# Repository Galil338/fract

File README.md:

# Fract Keyboard

Fract is a 34 key ortholinear keyboard, powered by a bluetooth-enabled Pro Micro compatible dev board.

It uses Choc v1 keyswitches with 18mm x 17mm spacing.

The goal of this design was to build a simple pocketable keyboard out of PCBs.

## Project structure

* [`gerbers`](gerbers): Gerber files for PCB manufacturing
* [`graphics`](graphics): Source assets for PCB silkscreen
* [`kicad`](kicad): KiCad project files (schematics and PCB designs)
* [`kicad-libraries`](kicad-libraries): KiCad components and footprints
* [`images`](images): Images for project documentation

## PCBs

**Each build uses two copies of the main PCB and two copies of the top plate PCB.**

The main PCB is used as the logical PCB. A second copy of the main PCB is used a bottom plate, by flipping it the long way and screwing it directly to the logical PCB.

Two copies of the top plate PCB cover the dev board and battery. Flip this PCB as well. It has a cutout which fits the reset button on the left, and the power switch on the right.

## Keyboard firmware

* ZMK
    * Fract shield definition is in [skarrmann's zmk-config](https://github.com/skarrmann/zmk-config)

## Bill of materials

Part | Purpose | Quantity | Notes
---- | ------- | -------- | ---------
Main PCB  | logical PCB, bottom plate | 2 | Send Gerber zip files to [JLCPCB](https://jlcpcb.com/)
Top plate PCB  | cover dev board and battery  | 2 | 
Bluetooth Pro Micro | Microcontroller board | 1 | nice!nano or SuperMini nRF52840
502040 LiPo Battery | Powers the wireless keyboard | 1 | JST PH 2.0 connector, ~5cm wire length
S2B-PH-K-S connector | JST PH 2.0 battery connector | 1 |
SS12D00, 5mm handle length | On/Off switch | 1 |
6mm x 6mm push button, 8mm total height | Reset button | 1 |
1N4148 SOD-123 | Diodes for keyboard row-column matrix | 34 |
Choc v1 Keyswitches |  | 34 |
Choc v1 Keycaps |  | 34 | Use keycaps which fit 18mm x 17mm spacing
M2 5mm screws | Screws PCBs together | 19 |
M2 6mm spacers | Spacers between logical PCB and top plates | 8 |
M2 nuts | Holds the top screws between the bottom plate and logical PCB | 3 |
[Peel-a-way Sockets and Pins](https://ringerkeys.com/collections/modders-tools/products/peel-a-way-sockets) | socket dev board to PCB | 2 strips of 12 pins/sockets | May use other low profile sockets which give less than 6 mm total height.

## PCB manufacturing settings

These are the manufacturing settings I used when ordering from JLCPCB:

* **Base Material**: FR4
* **Layers**: 2
* **Dimensions**: (whatever the gerber file specifies)
* **PCB Qty**: 5
* **Different Design**: 1
* **Delivery Format**: Single PCB
* **PCB Thickness**: 1.6
* **PCB Color**: Black
* **Silkscreen**: White
* **Surface Finish**: LeadFree HASL-RoHS
* **Outer Copper Weight**: 1 oz
* **Gold Fingers**: No
* **Confirm Production File**: No
* **Flying Probe Test**: Fully Test
* **Castellated Holes**: No
* **Mark on PCB**: Remove Mark

## Build tips

* Before starting, check if the PCBs are warped, and bend them to be perfectly flat before soldering.
* Make sure the diodes are oriented correctly, cathode on the side with the line! Once the keyswitches are soldered in, you won't be able to get to them anymore.
* Make sure the dev board is placed **components side up**. The pinout labels printed on the PCB should align with those printed on the dev board.
    * 
* While soldering the the battery connector, reset button, and power switch, use tape to temporarily hold them in place. Solder just one leg of each of these components, make sure they are aligned correctly, and then solder the other legs. Clip the legs of the power switch since they are longer than the bottom plate.
    * 
* Don't plug in the battery until you're done soldering everything! **MAKE SURE THE BLACK WIRE (-) IS ON TOP AND THE RED WIRE (+) IS ON BOTTOM, OR YOU'LL FRY YOUR DEV BOARD!** Use tape to secure the battery and its wires.
    * 

## KiCad project notes

The top plate was generated with the [Horizon Board Producer KiCad plugin](https://github.com/skarrmann/horizon#kicad-project-notes).

## Revision history

* Fract 1.0 (2024-10-16)
    * Initial Choc switch PCB design

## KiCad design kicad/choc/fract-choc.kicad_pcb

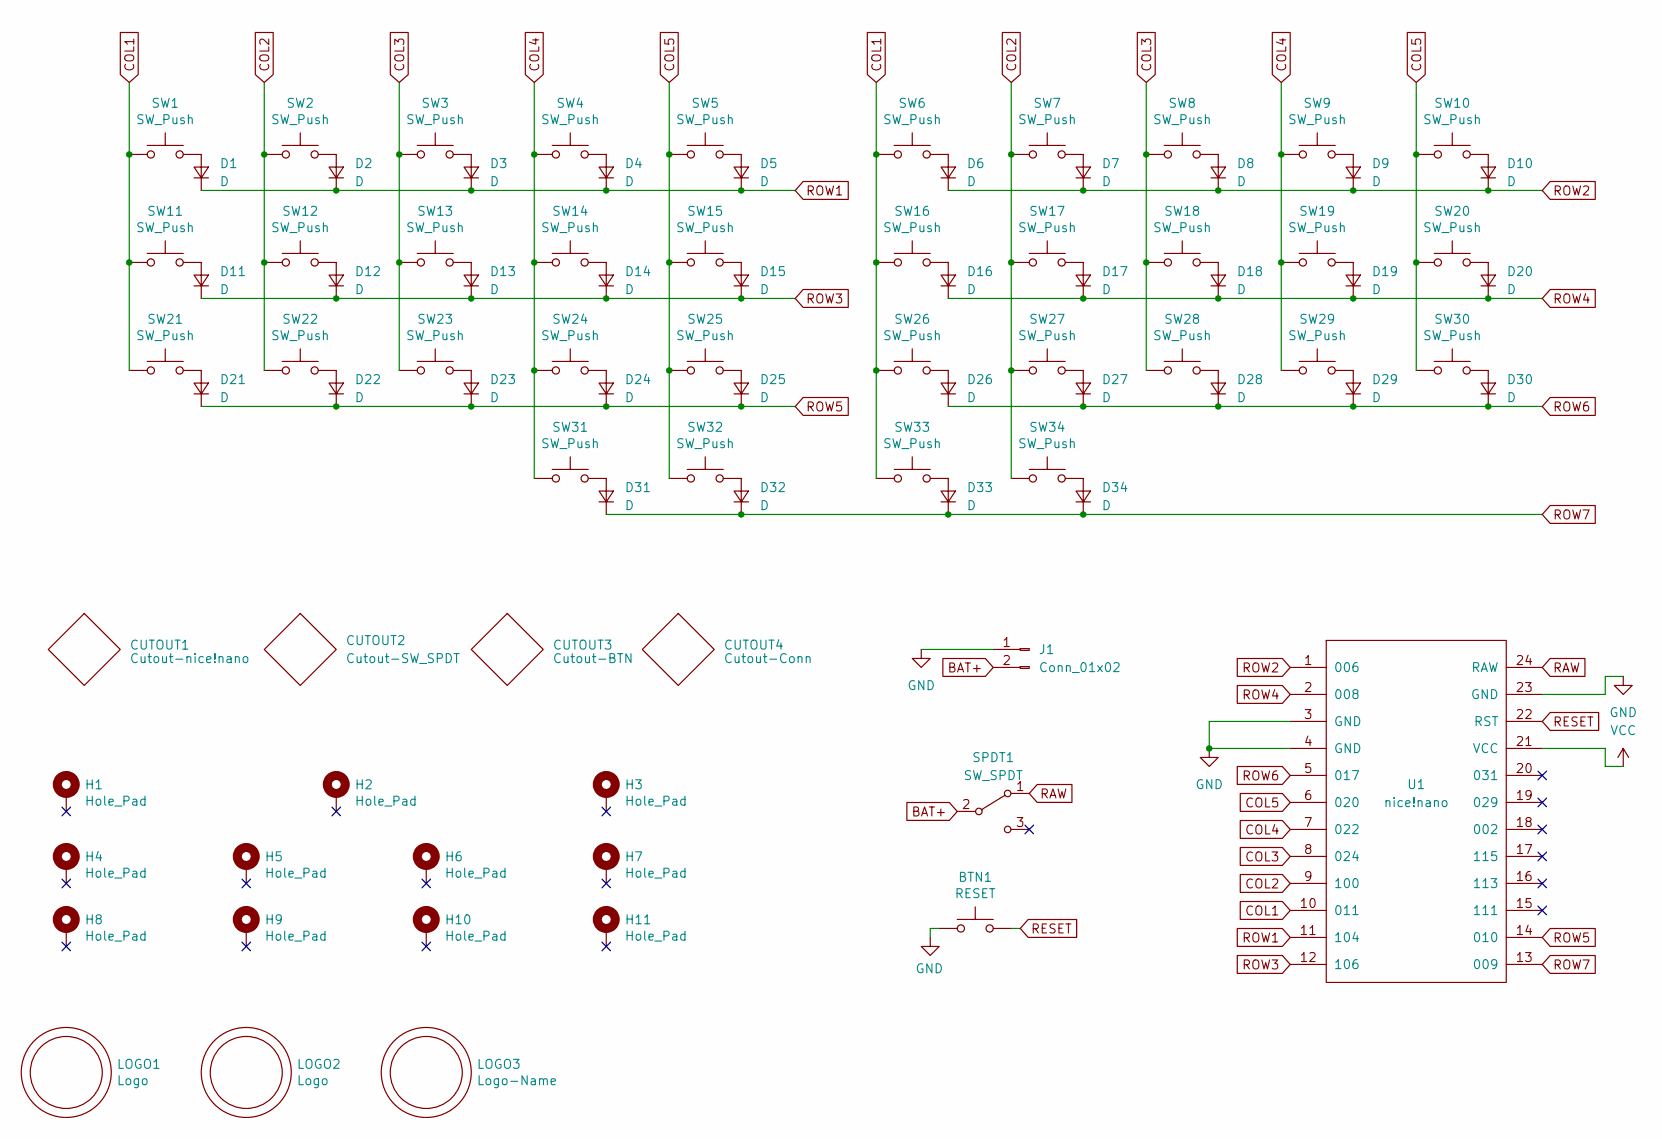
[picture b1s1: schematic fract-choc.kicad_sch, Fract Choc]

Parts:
BTN1: RESET; SW_Push_6mm
CUTOUT1: Cutout-nice!nano; Cutout_nice!nano
CUTOUT2: Cutout-SW_SPDT; Cutout_SW_SS12D00
CUTOUT3: Cutout-BTN; Cutout_SW_Push_6mm
CUTOUT4: Cutout-Conn; Cutout_JST_PH_S2B-PH-K_1x02_P2.00mm_Horizontal
D1, D2, D3, D4, D5, D6, D7, D8, D9, D10, D11, D12, D13, D14, D15, D16, D17, D18, D19, D20, D21, D22, D23, D24, D25, D26, D27, D28, D29, D30, D31, D32, D33, D34: D; D_SOD-123
H1, H2, H3, H4, H5, H6, H7, H8, H9, H10, H11: Hole_Pad; Mount_M2
J1: Conn_01x02; JST_PH_S2B-PH-K_1x02_P2.00mm_Horizontal
LOGO1, LOGO2: Logo; Logo_Fract
LOGO3: Logo-Name; Logo_Fract_Name
SPDT1: SW_SPDT; SW_SS12D00
SW1, SW2, SW3, SW4, SW5, SW6, SW7, SW8, SW9, SW10, SW11, SW12, SW13, SW14, SW15, SW16, SW17, SW18, SW19, SW20, SW21, SW22, SW23, SW24, SW25, SW26, SW27, SW28, SW29, SW30, SW31, SW32, SW33, SW34: SW_Push; SW_Choc
U1: nice!nano

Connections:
BAT+: J1.2, SPDT1.2 (B)
COL1: SW1.1, SW6.1, SW11.1, SW16.1, SW21.1, SW26.1, SW33.1, U1.10 (011)
COL2: SW2.1, SW7.1, SW12.1, SW17.1, SW22.1, SW27.1, SW34.1, U1.9 (100)
COL3: SW3.1, SW8.1, SW13.1, SW18.1, SW23.1, SW28.1, U1.8 (024)
COL4: SW4.1, SW9.1, SW14.1, SW19.1, SW24.1, SW29.1, SW31.1, U1.7 (022)
COL5: SW5.1, SW10.1, SW15.1, SW20.1, SW25.1, SW30.1, SW32.1, U1.6 (020)
GND: BTN1.2, J1.1, U1.3 (GND), U1.4 (GND), U1.23 (GND)
unnamed: D1.2 (A), SW1.2
unnamed: D2.2 (A), SW2.2
unnamed: D3.2 (A), SW3.2
unnamed: D4.2 (A), SW4.2
unnamed: D5.2 (A), SW5.2
unnamed: D6.2 (A), SW6.2
unnamed: D7.2 (A), SW7.2
unnamed: D8.2 (A), SW8.2
unnamed: D9.2 (A), SW9.2
unnamed: D10.2 (A), SW10.2
unnamed: D11.2 (A), SW11.2
unnamed: D12.2 (A), SW12.2
unnamed: D13.2 (A), SW13.2
unnamed: D14.2 (A), SW14.2
unnamed: D15.2 (A), SW15.2
unnamed: D16.2 (A), SW16.2
unnamed: D17.2 (A), SW17.2
unnamed: D18.2 (A), SW18.2
unnamed: D19.2 (A), SW19.2
unnamed: D20.2 (A), SW20.2
unnamed: D21.2 (A), SW21.2
unnamed: D22.2 (A), SW22.2
unnamed: D23.2 (A), SW23.2
unnamed: D24.2 (A), SW24.2
unnamed: D25.2 (A), SW25.2
unnamed: D26.2 (A), SW26.2
unnamed: D27.2 (A), SW27.2
unnamed: D28.2 (A), SW28.2
unnamed: D29.2 (A), SW29.2
unnamed: D30.2 (A), SW30.2
unnamed: D31.2 (A), SW31.2
unnamed: D32.2 (A), SW32.2
unnamed: D33.2 (A), SW33.2
unnamed: D34.2 (A), SW34.2
RAW: SPDT1.1 (A), U1.24 (RAW)
RESET: BTN1.1, U1.22 (RST)
ROW1: D1.1 (K), D2.1 (K), D3.1 (K), D4.1 (K), D5.1 (K), U1.11 (104)
ROW2: D6.1 (K), D7.1 (K), D8.1 (K), D9.1 (K), D10.1 (K), U1.1 (006)
ROW3: D11.1 (K), D12.1 (K), D13.1 (K), D14.1 (K), D15.1 (K), U1.12 (106)
ROW4: D16.1 (K), D17.1 (K), D18.1 (K), D19.1 (K), D20.1 (K), U1.2 (008)
ROW5: D21.1 (K), D22.1 (K), D23.1 (K), D24.1 (K), D25.1 (K), U1.14 (010)
ROW6: D26.1 (K), D27.1 (K), D28.1 (K), D29.1 (K), D30.1 (K), U1.5 (017)
ROW7: D31.1 (K), D32.1 (K), D33.1 (K), D34.1 (K), U1.13 (009)
VCC: U1.21 (VCC)

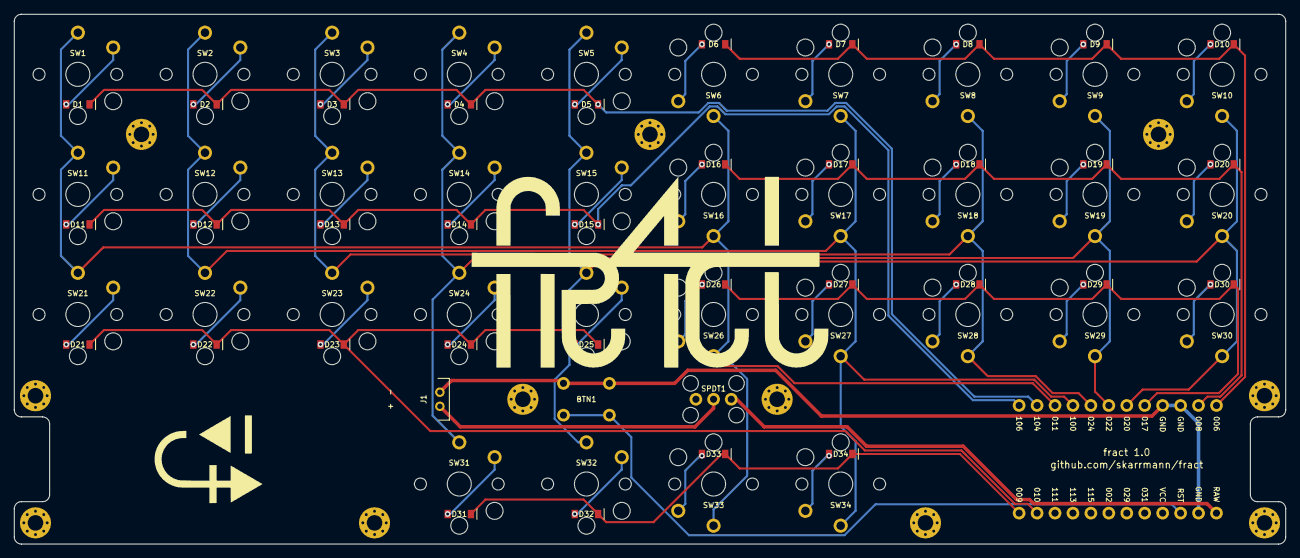
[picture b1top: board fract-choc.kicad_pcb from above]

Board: 2 copper layers, 180.0 x 75.0 mm, 90 parts (1 on the bottom side), 50 nets.

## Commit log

2024-10-03 Implement initial design
2024-10-17 Convert to 34 keys with top plates
2024-10-20 Clean up design files
2024-11-12 Change on/off switch part
2024-11-13 Add PCB notes
2024-11-13 Add images
